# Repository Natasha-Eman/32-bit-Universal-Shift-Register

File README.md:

# Modular 32-bit Universal Shift Register

## Repository Contents

- 📄 Documentation
- 🖥️ Logisim Designs
- 📐 KiCad Schematics
- 🛠 PCB Layouts
- 📦 Gerber Files
- 🎨 3D PCB Models

## Table of Contents

- [Overview](#overview)
- [Key Features](#key-features)
- [Project Development](#project-development)
- [Design Decisions](#design-decisions)
- [Project Structure](#project-structure)
- [Software & Tools Used](#software--tools-used)
- [Design Files](#design-files)
- [Future Improvements](#future-improvements)
- [License](#license)
- [Author](#author)

## Overview

This project presents the design and implementation of a **modular 32-bit Universal Shift Register (USR)**, developed as a personal learning project during my BS Electrical Engineering studies.

The project began with digital logic design in **Logisim Evolution**, where the complete Universal Shift Register was designed and verified from the gate level. After validating the logic, the design was implemented in **KiCad** as a modular hardware system consisting of two printed circuit boards:

- **Main Logic Board** – Implements the core Universal Shift Register logic.
- **Interface Board** – Provides LEDs, current-limiting resistors, and headers for visualization and user interaction.

The modular architecture improves maintainability, simplifies debugging, and allows the logic board to be reused independently of the user interface.

The repository contains the complete design process, including digital logic, schematics, PCB layouts, 3D models, manufacturing files, and project documentation.

## Key Features
- Modular 32-bit Universal Shift Register architecture
- Custom digital logic designed and verified in Logisim Evolution
- Two-board PCB architecture developed in KiCad
- Main Logic Board and separate Interface Board
- Complete schematic capture and PCB layout
- Design Rule Check (DRC) completed with zero errors
- Manufacturing-ready Gerber and Drill files
- 3D PCB visualization
- Modular design for easier debugging and future expansion

# Project Specifications

| Item | Description |
|------|-------------|
| Register Width | 32-bit |
| Core Logic IC | 74LS194 Universal Shift Register |
| PCB Design Software | KiCad |
| Logic Design Software | Logisim Evolution |
| Architecture | Modular Two-Board Design |
| DRC Status | Passed (0 Errors) |
| Manufacturing Files | Included |

The project was developed incrementally, beginning with digital logic verification before progressing to PCB implementation and manufacturing-ready outputs.

## Project Development

## Digital Logic Design (Logisim Evolution)

The following figures illustrate the progression of the project from digital logic design to PCB implementation.

| 4:1 Multiplexer | 1-bit Universal Shift Register |
|-----------------|-------------------------------|
|  |  |

*Figure 1. Custom multiplexer (left) and 1-bit Universal Shift Register (right).*

<br>

| Complete 32-bit Universal Shift Register |
|------------------------------------------|
|  |

*Figure 2. Complete 32-bit Universal Shift Register verified in Logisim Evolution.*

## Hardware Implementation (KiCad)

### Main Logic Board

| PCB Layout | Schematic |
|------------|-----------|
|  |  |

*Figure 4. PCB Layout (left) and Schematic (right) of the Main Logic Board.*

<br>

| Modular Slice PCB | 3D View |
|-------------------|---------|
|  |  |

*Figure 5. Modular PCB slice (left) and 3D rendering (right) of the Main Logic Board.*

### Interface Board

| PCB Layout | Schematic |
|------------|-----------|
|  |  |

*Figure 6. PCB Layout (left) and Schematic (right) of the Interface Board.*

<br>

| 3D View |
|----------|
|  |

*Figure 7. 3D rendering of the Interface Board.*

## Design Decisions

Several engineering decisions were made during the development of this project to improve modularity, maintainability, and ease of debugging.

### Modular Hardware Architecture

Rather than combining the complete system onto a single PCB, the design was divided into two independent boards:

- **Main Logic Board** – Implements the Universal Shift Register logic.
- **Interface Board** – Contains LEDs, current-limiting resistors, and user interface headers.

Separating the interface circuitry from the logic circuitry results in a cleaner PCB layout, simplifies routing, and allows the logic board to be reused with different interface modules.

### Engineering Workflow

Instead of designing the hardware directly, the project followed a structured engineering workflow:

1. Design and verify the logic in Logisim Evolution.
2. Validate the complete 32-bit architecture.
3. Design the hardware implementation in KiCad.
4. Perform PCB Design Rule Checking (DRC).
5. Generate manufacturing-ready Gerber and Drill files.

This workflow reduced design errors before hardware implementation and provided confidence in the final PCB design.

## Project Structure

```

32-bit-Universal-Shift-Register
├── Datasheets/
├── Gerber/
│   ├── Logic_Board/
│   └── Interface_Board/
├── Images/
├── KiCad/
│   ├── Logic Board/
│   └── Interface Board/
├── Logisim/
├── README.md
└── LICENSE

## Software & Tools Used

| Software | Purpose |
|----------|---------|
| Logisim Evolution | Digital logic design and verification |
| KiCad | Schematic capture, PCB layout, and 3D visualization |
| Git | Version control |
| GitHub | Project hosting and documentation |

## Design Files

The repository includes all files required to study, modify, or manufacture the project:

- Logisim Evolution project files
- KiCad schematic files
- KiCad PCB layout files
- 3D PCB models
- Manufacturing-ready Gerber files
- Drill files
- Images and documentation

## Future Improvements

Possible future enhancements include:

- Hardware testing using fabricated PCBs
- Functional verification of the complete 32-bit hardware
- Integration with FPGA or microcontroller-based systems
- Expansion into larger modular register architectures

## License

This project is released under the MIT License.

## Author

**Natasha Eman**

BS Electrical Engineering Student
FAST National University of Computer and Emerging Sciences (FAST-NUCES)

GitHub: https://github.com/Natasha-Eman

<<<<<<< HEAD
### Technologies & Tools

- KiCad
- Logisim Evolution
- Python
- OpenCV
- Git & GitHub

---

This project represents my journey from digital logic simulation to PCB implementation, with the goal of strengthening my understanding of practical hardware design and engineering workflows.

I welcome constructive feedback and suggestions for improving both the design and the documentation.
=======
LinkedIn: https://www.linkedin.com/in/natasha-eman-368531329
>>>>>>> ecc2cd1 (Refactor project into modular two-board architecture and update documentation)

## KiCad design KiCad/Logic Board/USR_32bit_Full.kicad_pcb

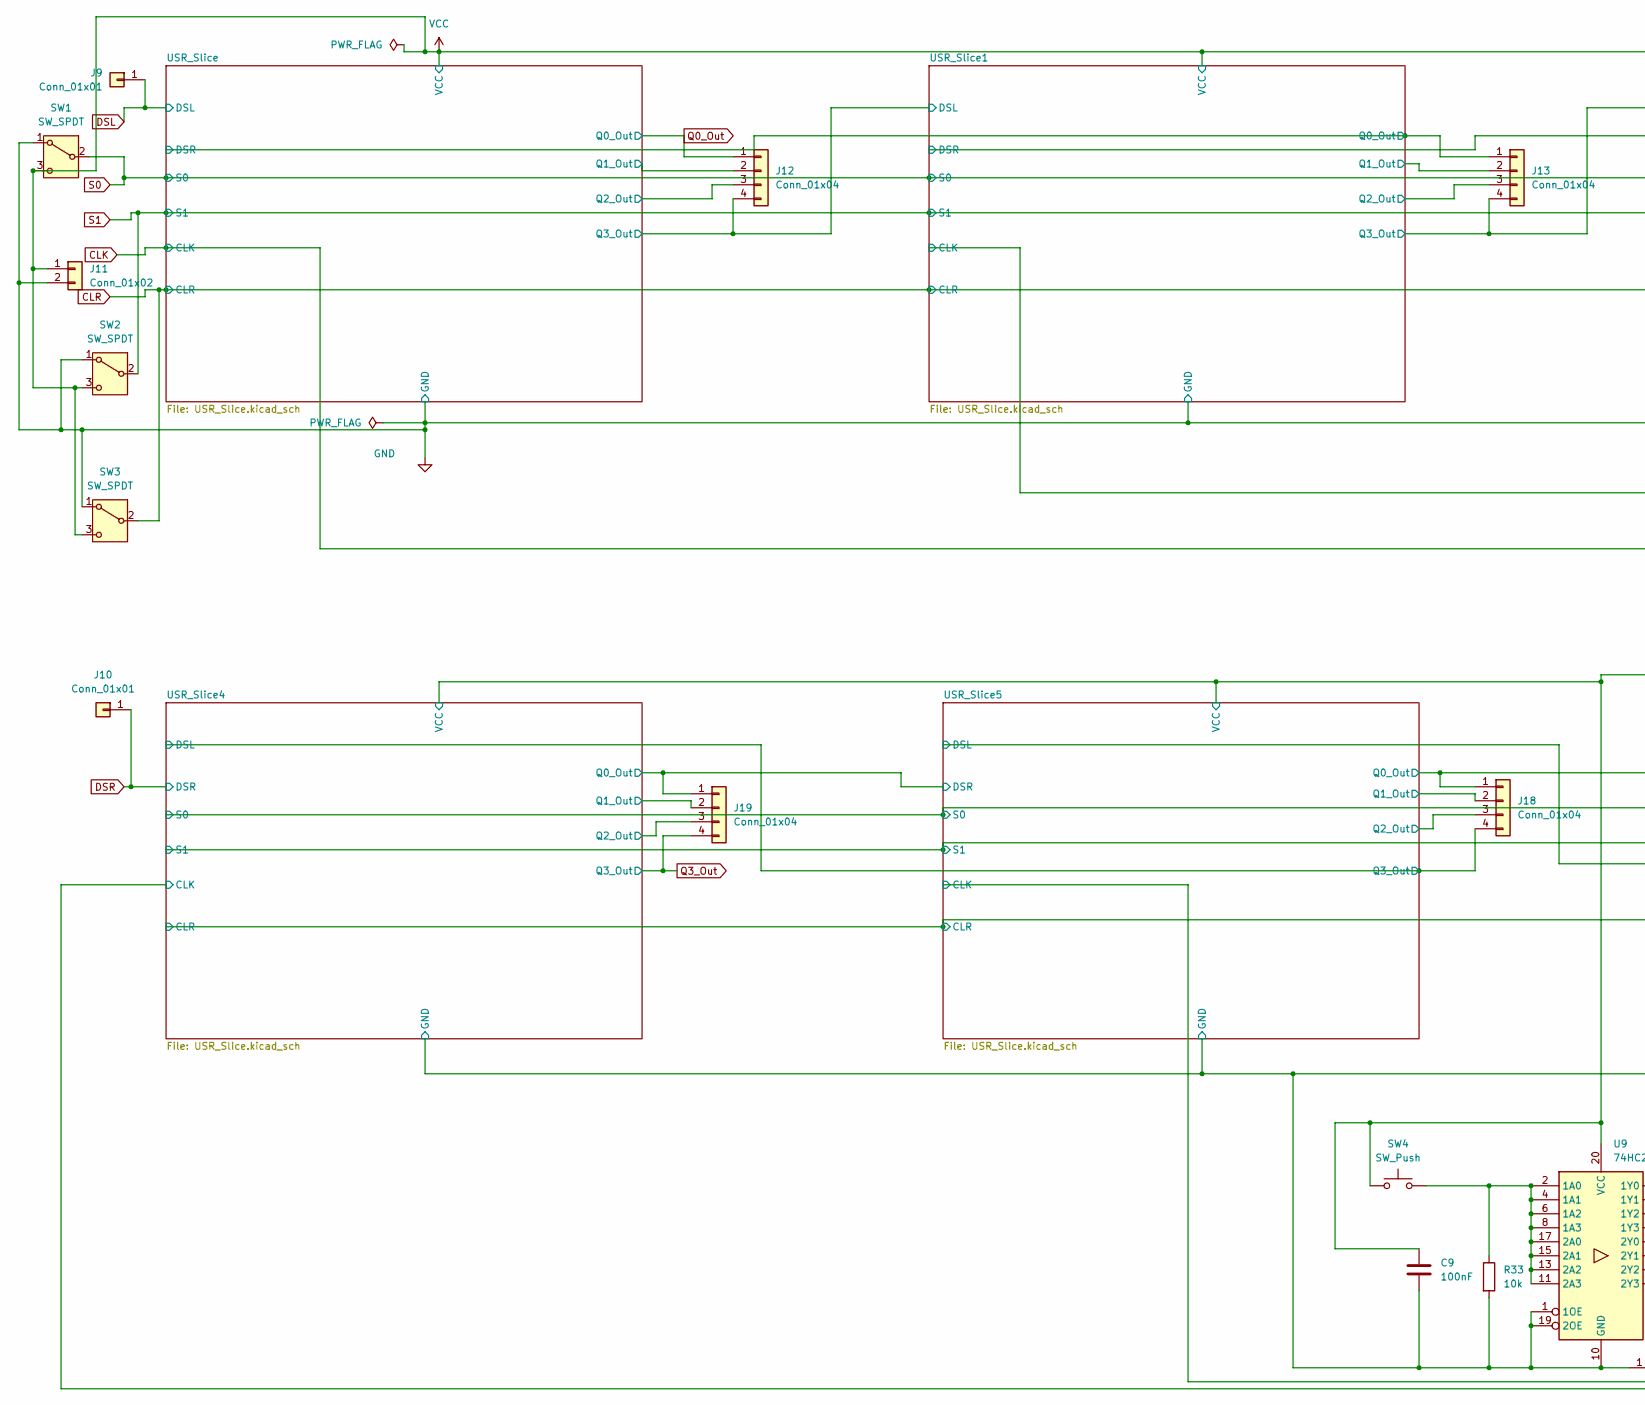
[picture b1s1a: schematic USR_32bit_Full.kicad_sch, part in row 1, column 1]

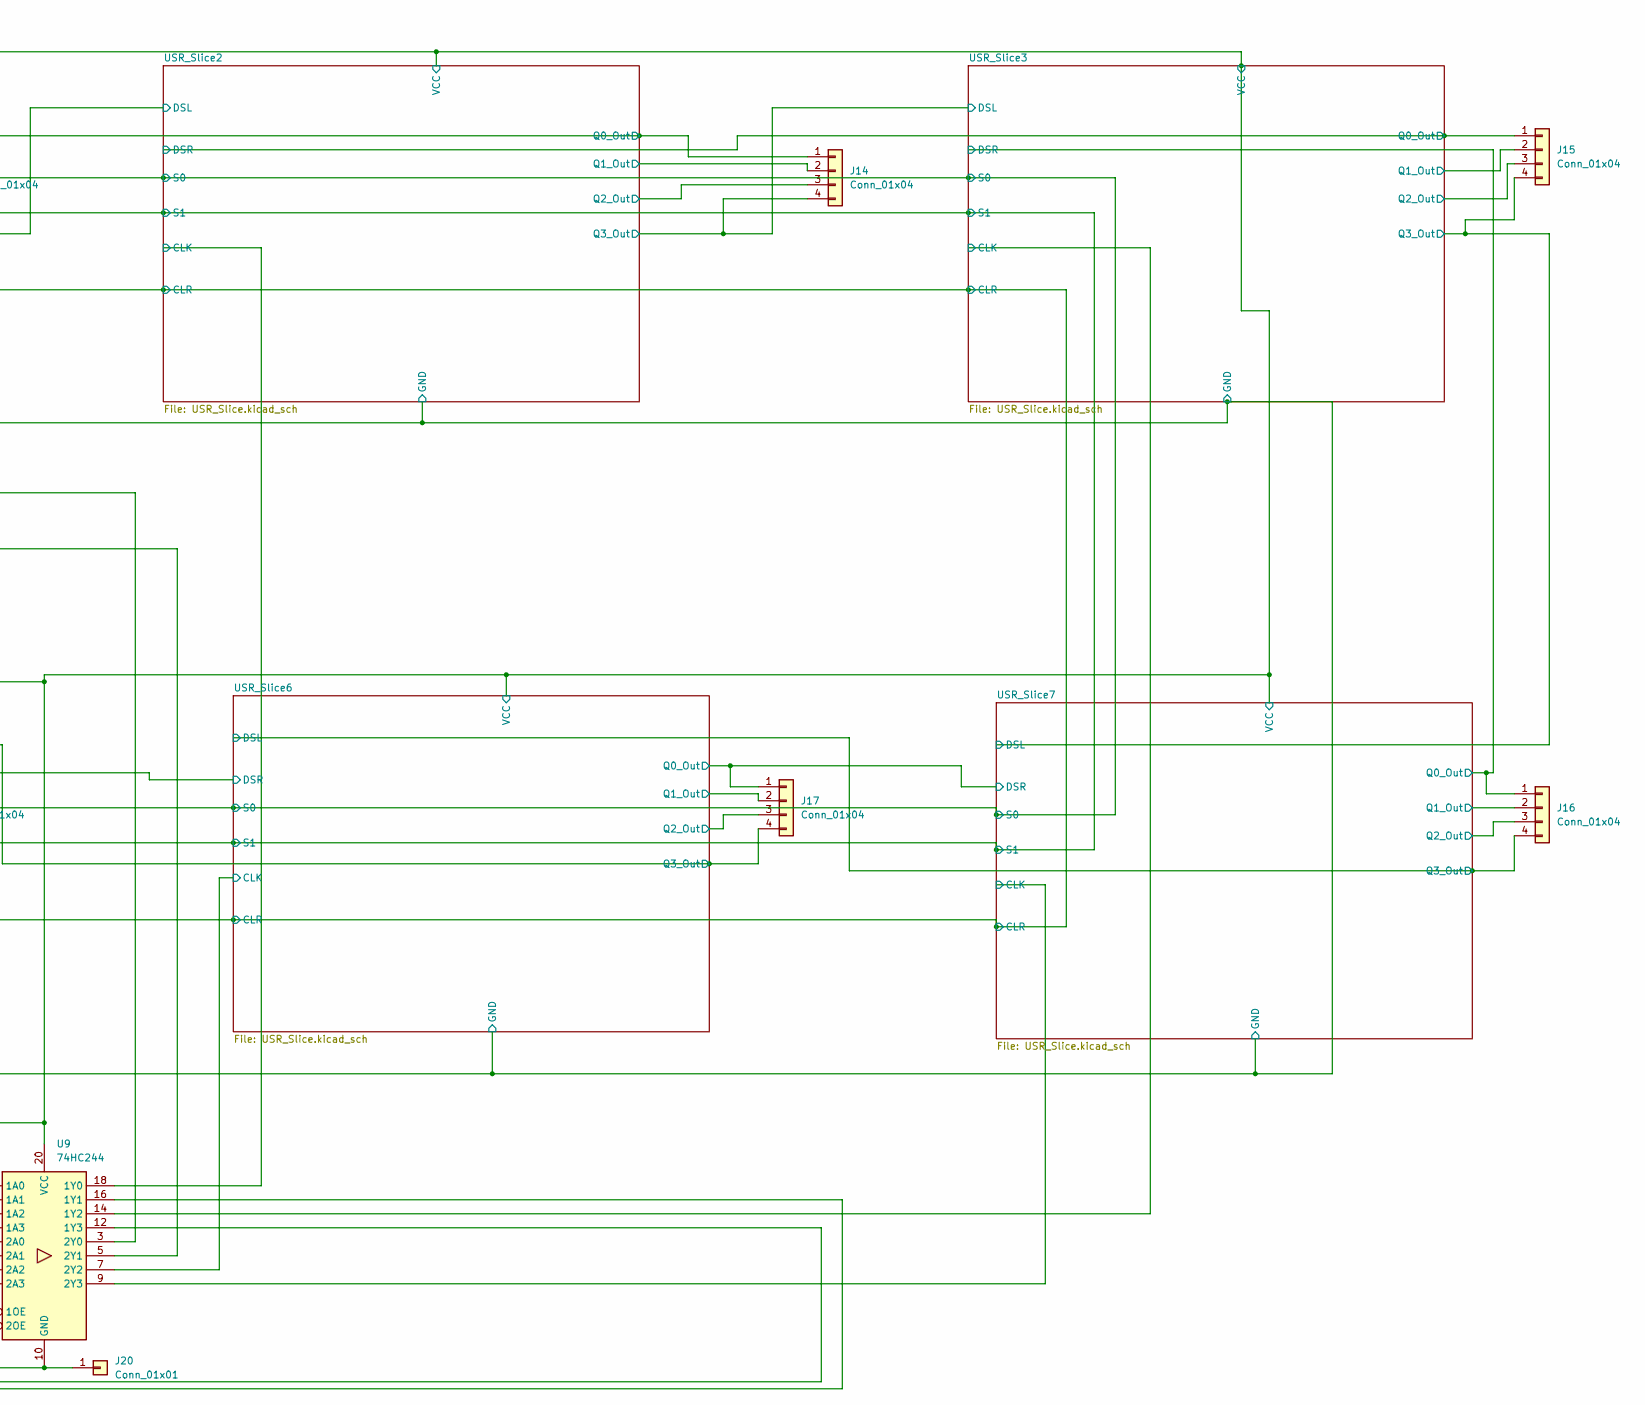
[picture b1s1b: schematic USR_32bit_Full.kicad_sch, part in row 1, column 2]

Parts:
C9: 100nF; C_Disc_D3.0mm_W2.0mm_P2.50mm
J9, J10: Conn_01x01; PinHeader_1x01_P2.54mm_Vertical
J11: Conn_01x02; PinHeader_1x02_P2.54mm_Vertical
J12, J13, J14, J15, J16, J17, J18, J19: Conn_01x04; PinHeader_1x04_P2.54mm_Vertical
J20: Conn_01x01; PinSocket_1x01_P2.54mm_Vertical
R33: 10k; R_Axial_DIN0207_L6.3mm_D2.5mm_P10.16mm_Horizontal
SW1, SW2, SW3: SW_SPDT; SW_Slide_SPDT_Straight_CK_OS102011MS2Q
SW4: SW_Push; SW_PUSH_6mm
U9: 74HC244; DIP-20_W7.62mm

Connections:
/USR_Slice1/CLK: U9.3 (2Y0); also elsewhere on the board
/USR_Slice1/DSR: J14.1; also elsewhere on the board
/USR_Slice1/Q1_Out: J13.2; also elsewhere on the board
/USR_Slice1/Q2_Out: J13.3; also elsewhere on the board
/USR_Slice1/Q3_Out: J13.4; also elsewhere on the board
/USR_Slice2/CLK: U9.18 (1Y0); also elsewhere on the board
/USR_Slice2/DSR: J15.1; also elsewhere on the board
/USR_Slice2/Q1_Out: J14.2; also elsewhere on the board
/USR_Slice2/Q2_Out: J14.3; also elsewhere on the board
/USR_Slice2/Q3_Out: J14.4; also elsewhere on the board
/USR_Slice3/CLK: U9.14 (1Y2); also elsewhere on the board
/USR_Slice3/DSR: J16.1; also elsewhere on the board
/USR_Slice3/Q1_Out: J15.2; also elsewhere on the board
/USR_Slice3/Q2_Out: J15.3; also elsewhere on the board
/USR_Slice3/Q3_Out: J15.4; also elsewhere on the board
/USR_Slice4/CLK: U9.16 (1Y1); also elsewhere on the board
/USR_Slice4/DSL: J18.4; also elsewhere on the board
/USR_Slice4/Q0_Out: J19.1; also elsewhere on the board
/USR_Slice4/Q1_Out: J19.2; also elsewhere on the board
/USR_Slice4/Q2_Out: J19.3; also elsewhere on the board
/USR_Slice5/CLK: U9.12 (1Y3); also elsewhere on the board
/USR_Slice5/DSL: J17.4; also elsewhere on the board
/USR_Slice5/Q0_Out: J18.1; also elsewhere on the board
/USR_Slice5/Q1_Out: J18.2; also elsewhere on the board
/USR_Slice5/Q2_Out: J18.3; also elsewhere on the board
/USR_Slice6/CLK: U9.7 (2Y2); also elsewhere on the board
/USR_Slice6/DSL: J16.4; also elsewhere on the board
/USR_Slice6/Q0_Out: J17.1; also elsewhere on the board
/USR_Slice6/Q1_Out: J17.2; also elsewhere on the board
/USR_Slice6/Q2_Out: J17.3; also elsewhere on the board
/USR_Slice7/CLK: U9.9 (2Y3); also elsewhere on the board
/USR_Slice7/Q1_Out: J16.2; also elsewhere on the board
/USR_Slice7/Q2_Out: J16.3; also elsewhere on the board
/USR_Slice/DSR: J13.1; also elsewhere on the board
/USR_Slice/Q1_Out: J12.2; also elsewhere on the board
/USR_Slice/Q2_Out: J12.3; also elsewhere on the board
/USR_Slice/Q3_Out: J12.4; also elsewhere on the board
CLK: U9.5 (2Y1); also elsewhere on the board
CLR: SW3.2 (B); also elsewhere on the board
DSL: J9.1 (Pin_1_1); also elsewhere on the board
DSR: J10.1 (Pin_1_1); also elsewhere on the board
GND: C9.2, J11.2, J20.1 (Pin_1_1), R33.2, SW1.1 (A), SW2.1 (A), SW3.1 (A), U9.1 (1OE), U9.10 (GND), U9.19 (2OE); also elsewhere on the board
unnamed: R33.1, SW4.2, U9.2 (1A0), U9.4 (1A1), U9.6 (1A2), U9.8 (1A3), U9.11 (2A3), U9.13 (2A2), U9.15 (2A1), U9.17 (2A0)
Q0_Out: J12.1; also elsewhere on the board
Q3_Out: J19.4; also elsewhere on the board
S0: SW1.2 (B); also elsewhere on the board
S1: SW2.2 (B); also elsewhere on the board
VCC: C9.1, J11.1, SW1.3 (C), SW2.3 (C), SW3.3 (C), SW4.1, U9.20 (VCC); also elsewhere on the board

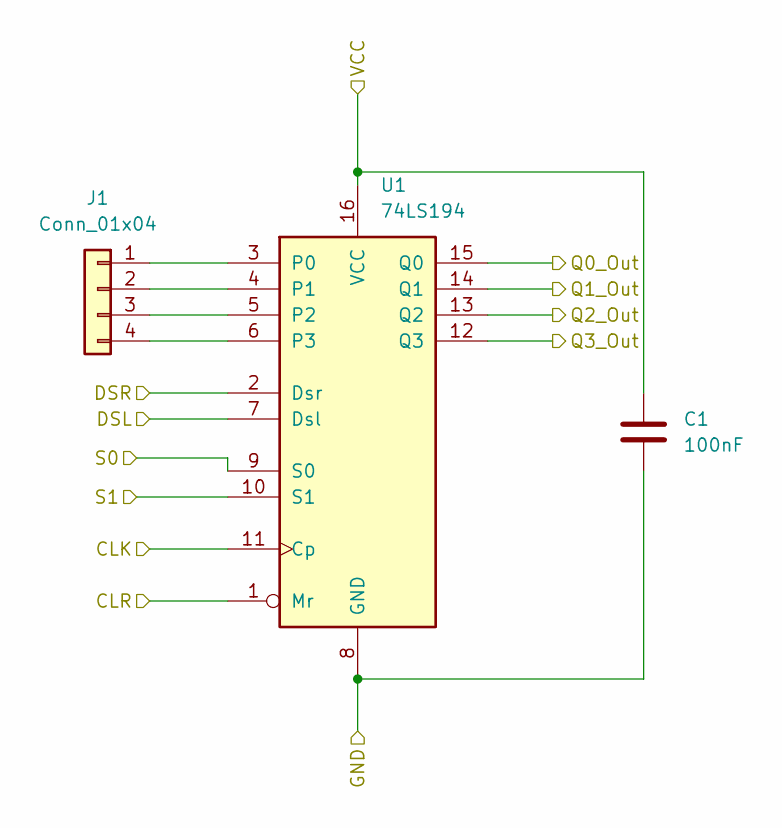
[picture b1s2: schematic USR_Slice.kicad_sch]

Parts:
C1: 100nF; C_Disc_D3.0mm_W2.0mm_P2.50mm
J1: Conn_01x04; PinHeader_1x04_P2.54mm_Vertical
U1: 74LS194; DIP-16_W7.62mm

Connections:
/USR_Slice/DSR: U1.2 (Dsr); also elsewhere on the board
/USR_Slice/Q1_Out: U1.14 (Q1); also elsewhere on the board
/USR_Slice/Q2_Out: U1.13 (Q2); also elsewhere on the board
/USR_Slice/Q3_Out: U1.12 (Q3); also elsewhere on the board
CLK: U1.11 (Cp); also elsewhere on the board
CLR: U1.1 (Mr); also elsewhere on the board
DSL: U1.7 (Dsl); also elsewhere on the board
GND: C1.2, U1.8 (GND); also elsewhere on the board
unnamed: J1.1, U1.3 (P0)
unnamed: J1.2, U1.4 (P1)
unnamed: J1.3, U1.5 (P2)
unnamed: J1.4, U1.6 (P3)
Q0_Out: U1.15 (Q0); also elsewhere on the board
S0: U1.9 (S0); also elsewhere on the board
S1: U1.10 (S1); also elsewhere on the board
VCC: C1.1, U1.16 (VCC); also elsewhere on the board

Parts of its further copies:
C2, C3, C4, C5, C6, C7, C8: 100nF; C_Disc_D3.0mm_W2.0mm_P2.50mm
J2, J3, J4, J5, J6, J7, J8: Conn_01x04; PinHeader_1x04_P2.54mm_Vertical
U2, U3, U4, U5, U6, U7, U8: 74LS194; DIP-16_W7.62mm

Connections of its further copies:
/USR_Slice1/CLK: U2.11 (Cp); also elsewhere on the board
/USR_Slice1/DSR: U2.2 (Dsr), U3.15 (Q0); also elsewhere on the board
/USR_Slice1/Q1_Out: U2.14 (Q1); also elsewhere on the board
/USR_Slice1/Q2_Out: U2.13 (Q2); also elsewhere on the board
/USR_Slice1/Q3_Out: U2.12 (Q3), U3.7 (Dsl); also elsewhere on the board
/USR_Slice2/CLK: U3.11 (Cp); also elsewhere on the board
/USR_Slice2/DSR: U3.2 (Dsr), U4.15 (Q0); also elsewhere on the board
/USR_Slice2/Q1_Out: U3.14 (Q1); also elsewhere on the board
/USR_Slice2/Q2_Out: U3.13 (Q2); also elsewhere on the board
/USR_Slice2/Q3_Out: U3.12 (Q3), U4.7 (Dsl); also elsewhere on the board
/USR_Slice3/CLK: U4.11 (Cp); also elsewhere on the board
/USR_Slice3/DSR: U4.2 (Dsr), U8.15 (Q0); also elsewhere on the board
/USR_Slice3/Q1_Out: U4.14 (Q1); also elsewhere on the board
/USR_Slice3/Q2_Out: U4.13 (Q2); also elsewhere on the board
/USR_Slice3/Q3_Out: U4.12 (Q3), U8.7 (Dsl); also elsewhere on the board
/USR_Slice4/CLK: U5.11 (Cp); also elsewhere on the board
/USR_Slice4/DSL: U5.7 (Dsl), U6.12 (Q3); also elsewhere on the board
/USR_Slice4/Q0_Out: U5.15 (Q0), U6.2 (Dsr); also elsewhere on the board
/USR_Slice4/Q1_Out: U5.14 (Q1); also elsewhere on the board
/USR_Slice4/Q2_Out: U5.13 (Q2); also elsewhere on the board
/USR_Slice5/CLK: U6.11 (Cp); also elsewhere on the board
/USR_Slice5/DSL: U6.7 (Dsl), U7.12 (Q3); also elsewhere on the board
/USR_Slice5/Q0_Out: U6.15 (Q0), U7.2 (Dsr); also elsewhere on the board
/USR_Slice5/Q1_Out: U6.14 (Q1); also elsewhere on the board
/USR_Slice5/Q2_Out: U6.13 (Q2); also elsewhere on the board
/USR_Slice6/CLK: U7.11 (Cp); also elsewhere on the board
/USR_Slice6/DSL: U7.7 (Dsl), U8.12 (Q3); also elsewhere on the board
/USR_Slice6/Q0_Out: U7.15 (Q0), U8.2 (Dsr); also elsewhere on the board
/USR_Slice6/Q1_Out: U7.14 (Q1); also elsewhere on the board
/USR_Slice6/Q2_Out: U7.13 (Q2); also elsewhere on the board
/USR_Slice7/CLK: U8.11 (Cp); also elsewhere on the board
/USR_Slice7/Q1_Out: U8.14 (Q1); also elsewhere on the board
/USR_Slice7/Q2_Out: U8.13 (Q2); also elsewhere on the board
/USR_Slice/DSR: U2.15 (Q0); also elsewhere on the board
/USR_Slice/Q3_Out: U2.7 (Dsl); also elsewhere on the board
CLR: U2.1 (Mr), U3.1 (Mr), U4.1 (Mr), U5.1 (Mr), U6.1 (Mr), U7.1 (Mr), U8.1 (Mr); also elsewhere on the board
DSR: U5.2 (Dsr); also elsewhere on the board
GND: C2.2, C3.2, C4.2, C5.2, C6.2, C7.2, C8.2, U2.8 (GND), U3.8 (GND), U4.8 (GND), U5.8 (GND), U6.8 (GND), U7.8 (GND), U8.8 (GND); also elsewhere on the board
unnamed: J2.1, U2.3 (P0)
unnamed: J2.2, U2.4 (P1)
unnamed: J2.3, U2.5 (P2)
unnamed: J2.4, U2.6 (P3)
unnamed: J3.1, U3.3 (P0)
unnamed: J3.2, U3.4 (P1)
unnamed: J3.3, U3.5 (P2)
unnamed: J3.4, U3.6 (P3)
unnamed: J4.1, U4.3 (P0)
unnamed: J4.2, U4.4 (P1)
unnamed: J4.3, U4.5 (P2)
unnamed: J4.4, U4.6 (P3)
unnamed: J5.1, U5.3 (P0)
unnamed: J5.2, U5.4 (P1)
unnamed: J5.3, U5.5 (P2)
unnamed: J5.4, U5.6 (P3)
unnamed: J6.1, U6.3 (P0)
unnamed: J6.2, U6.4 (P1)
unnamed: J6.3, U6.5 (P2)
unnamed: J6.4, U6.6 (P3)
unnamed: J7.1, U7.3 (P0)
unnamed: J7.2, U7.4 (P1)
unnamed: J7.3, U7.5 (P2)
unnamed: J7.4, U7.6 (P3)
unnamed: J8.1, U8.3 (P0)
unnamed: J8.2, U8.4 (P1)
unnamed: J8.3, U8.5 (P2)
unnamed: J8.4, U8.6 (P3)
Q3_Out: U5.12 (Q3); also elsewhere on the board
S0: U2.9 (S0), U3.9 (S0), U4.9 (S0), U5.9 (S0), U6.9 (S0), U7.9 (S0), U8.9 (S0); also elsewhere on the board
S1: U2.10 (S1), U3.10 (S1), U4.10 (S1), U5.10 (S1), U6.10 (S1), U7.10 (S1), U8.10 (S1); also elsewhere on the board
VCC: C2.1, C3.1, C4.1, C5.1, C6.1, C7.1, C8.1, U2.16 (VCC), U3.16 (VCC), U4.16 (VCC), U5.16 (VCC), U6.16 (VCC), U7.16 (VCC), U8.16 (VCC); also elsewhere on the board

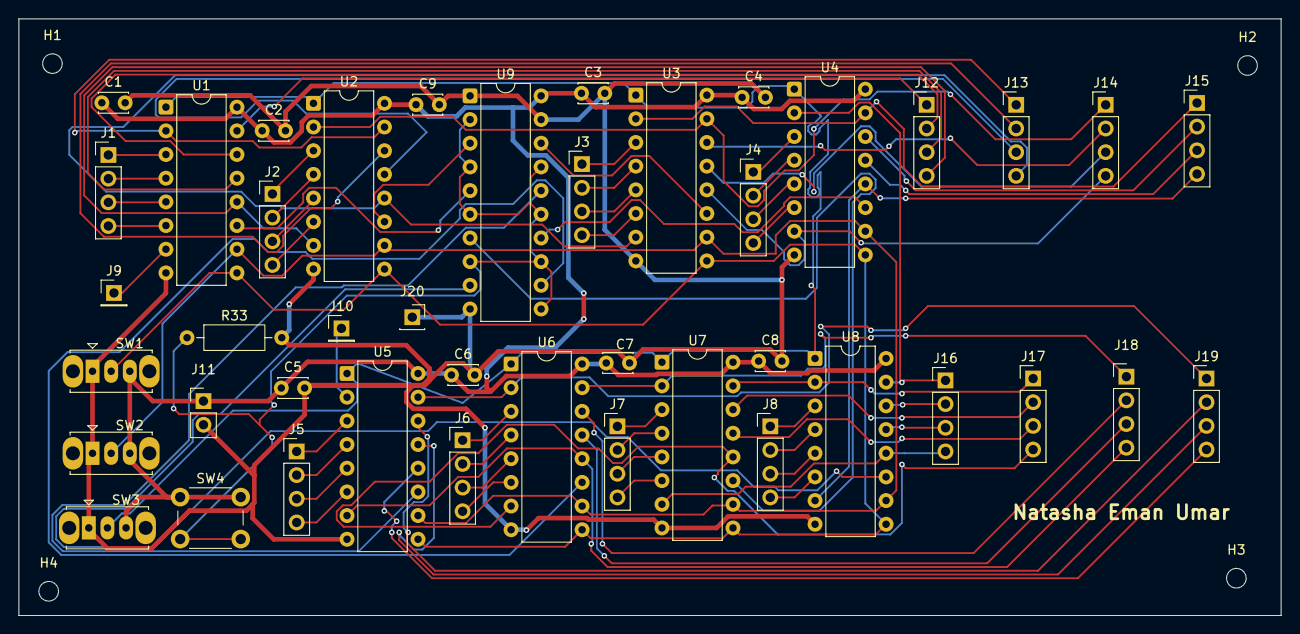
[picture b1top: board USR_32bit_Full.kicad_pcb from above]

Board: 2 copper layers, 135.4 x 64.0 mm, 47 parts (0 on the bottom side), 80 nets.

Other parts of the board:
H1, H2, H3, H4: MountingHole_2.1mm

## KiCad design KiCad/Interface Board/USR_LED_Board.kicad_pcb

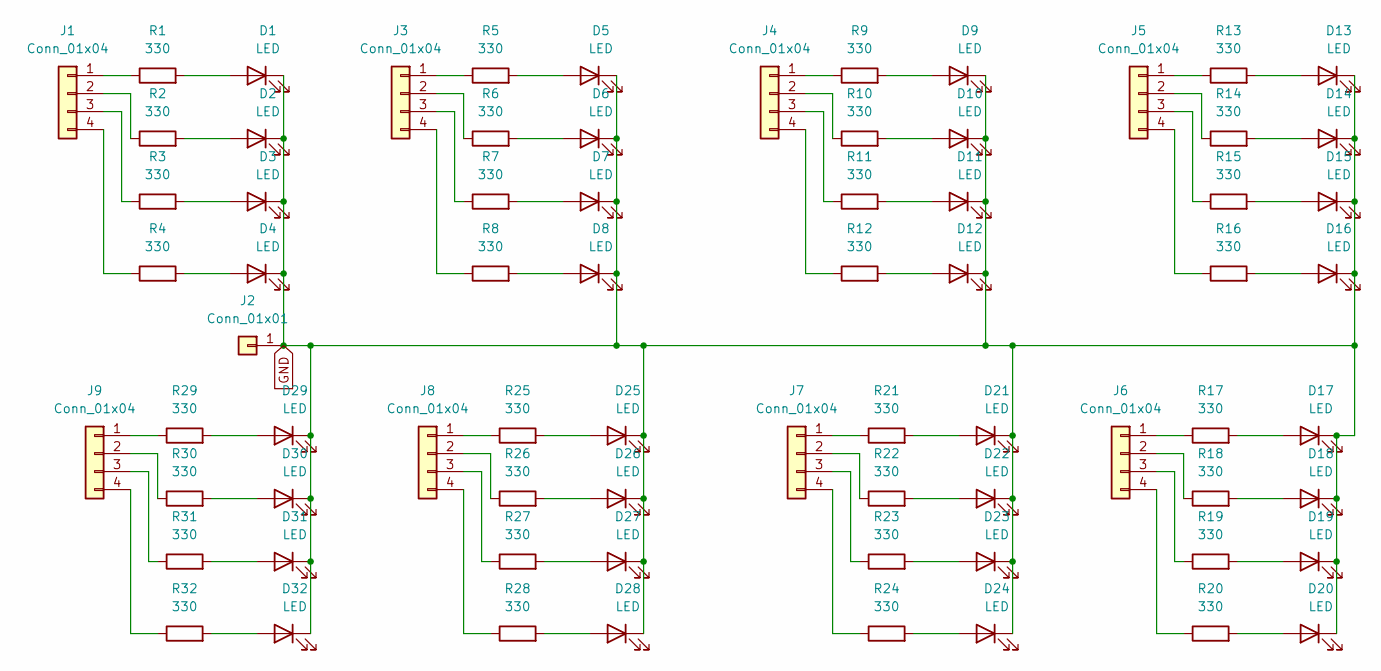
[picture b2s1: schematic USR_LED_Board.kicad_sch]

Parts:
D1, D2, D3, D4, D5, D6, D7, D8, D9, D10, D11, D12, D13, D14, D15, D16, D17, D18, D19, D20, D21, D22, D23, D24, D25, D26, D27, D28, D29, D30, D31, D32: LED; LED_D5.0mm
J1, J3, J4, J5, J6, J7, J8, J9: Conn_01x04; PinHeader_1x04_P2.54mm_Vertical
J2: Conn_01x01; PinHeader_1x01_P2.54mm_Vertical
R1, R2, R3, R4, R5, R6, R7, R8, R9, R10, R11, R12, R13, R14, R15, R16, R17, R18, R19, R20, R21, R22, R23, R24, R25, R26, R27, R28, R29, R30, R31, R32: 330; R_Axial_DIN0207_L6.3mm_D2.5mm_P10.16mm_Horizontal

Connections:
GND: D1.1 (K), D2.1 (K), D3.1 (K), D4.1 (K), D5.1 (K), D6.1 (K), D7.1 (K), D8.1 (K), D9.1 (K), D10.1 (K), D11.1 (K), D12.1 (K), D13.1 (K), D14.1 (K), D15.1 (K), D16.1 (K), D17.1 (K), D18.1 (K), D19.1 (K), D20.1 (K), D21.1 (K), D22.1 (K), D23.1 (K), D24.1 (K), D25.1 (K), D26.1 (K), D27.1 (K), D28.1 (K), D29.1 (K), D30.1 (K), D31.1 (K), D32.1 (K), J2.1 (Pin_1_1)
unnamed: D1.2 (A), R1.2
unnamed: D2.2 (A), R2.2
unnamed: D3.2 (A), R3.2
unnamed: D4.2 (A), R4.2
unnamed: D5.2 (A), R5.2
unnamed: D6.2 (A), R6.2
unnamed: D7.2 (A), R7.2
unnamed: D8.2 (A), R8.2
unnamed: D9.2 (A), R9.2
unnamed: D10.2 (A), R10.2
unnamed: D11.2 (A), R11.2
unnamed: D12.2 (A), R12.2
unnamed: D13.2 (A), R13.2
unnamed: D14.2 (A), R14.2
unnamed: D15.2 (A), R15.2
unnamed: D16.2 (A), R16.2
unnamed: D17.2 (A), R17.2
unnamed: D18.2 (A), R18.2
unnamed: D19.2 (A), R19.2
unnamed: D20.2 (A), R20.2
unnamed: D21.2 (A), R21.2
unnamed: D22.2 (A), R22.2
unnamed: D23.2 (A), R23.2
unnamed: D24.2 (A), R24.2
unnamed: D25.2 (A), R25.2
unnamed: D26.2 (A), R26.2
unnamed: D27.2 (A), R27.2
unnamed: D28.2 (A), R28.2
unnamed: D29.2 (A), R29.2
unnamed: D30.2 (A), R30.2
unnamed: D31.2 (A), R31.2
unnamed: D32.2 (A), R32.2
unnamed: J1.1, R1.1
unnamed: J1.2, R2.1
unnamed: J1.3, R3.1
unnamed: J1.4, R4.1
unnamed: J3.1, R5.1
unnamed: J3.2, R6.1
unnamed: J3.3, R7.1
unnamed: J3.4, R8.1
unnamed: J4.1, R9.1
unnamed: J4.2, R10.1
unnamed: J4.3, R11.1
unnamed: J4.4, R12.1
unnamed: J5.1, R13.1
unnamed: J5.2, R14.1
unnamed: J5.3, R15.1
unnamed: J5.4, R16.1
unnamed: J6.1, R17.1
unnamed: J6.2, R18.1
unnamed: J6.3, R19.1
unnamed: J6.4, R20.1
unnamed: J7.1, R21.1
unnamed: J7.2, R22.1
unnamed: J7.3, R23.1
unnamed: J7.4, R24.1
unnamed: J8.1, R25.1
unnamed: J8.2, R26.1
unnamed: J8.3, R27.1
unnamed: J8.4, R28.1
unnamed: J9.1, R29.1
unnamed: J9.2, R30.1
unnamed: J9.3, R31.1
unnamed: J9.4, R32.1

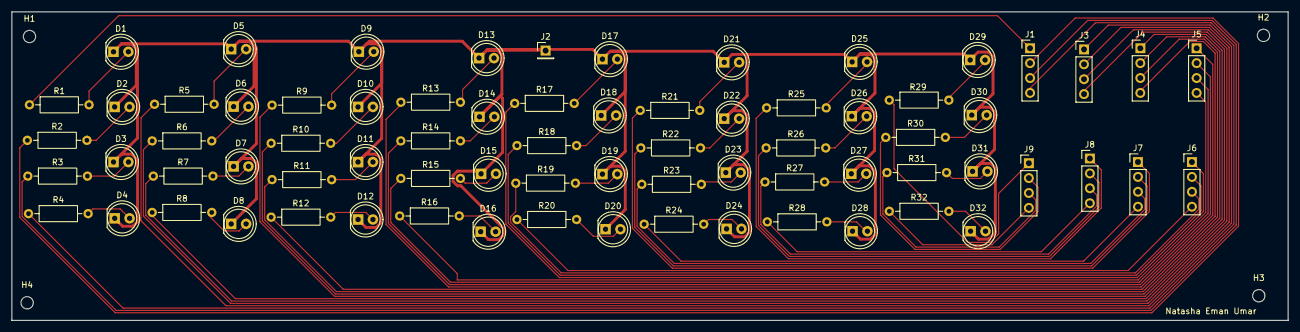
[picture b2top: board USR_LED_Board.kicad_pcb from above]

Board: 2 copper layers, 217.6 x 52.6 mm, 77 parts (0 on the bottom side), 65 nets.

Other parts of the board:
H1, H2, H3, H4: MountingHole_2.1mm
